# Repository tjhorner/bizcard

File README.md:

# PCBusiness Card

Hiya! Welcome to the documentation for my... business card? Yep, my business card. Which is also a PCB. Chances are you received one from me and are curious enough to scan the QR code on the back.

In these docs, you'll find information on the specs, how to flash it, which peripherals are onboard, how to do cool stuff with it, and (if you received a bare board) where to source the parts you'll need to assemble it. You'll also find the source KiCad project files for the schematic and board, as well as the source for the firmware that is installed by default. These are open source under CC-BY-SA 4.0 and MIT, so feel free to base your own designs on them.

## Directory Structure

- `docs`: Various documents about the project, including hardware info, flashing instructions, etc.
- `firmware`: Default firmware that ships with the board
- `pcb`: KiCad project files for the PCB

## Quick Start

If you want to check out all this board has to offer...

- Look at the docs for the [default firmware](docs/firmware.md). It goes in detail on what it does, and how you can connect to it to your computer via serial to enjoy the whole experience.
- Come back here to dive into the specs, then try your hand at [writing your own firmware](docs/flashing.md) (if you've programmed an Arduino before, it'll be a piece of cake).

After that, it's up to you! You can solder on some GPIO headers and connect whatever the heck you want and make it your own. Blinky Christmas lights? Sure! Doorbell? Why not! Pacemaker? Ok maybe not that. You have the full power of the RP2040 at your disposal, plus a hefty amount of flash you can use to store anything you want.

## Documentation

- [Bill of Materials](docs/bom.md)
- [Flashing Instructions](docs/flashing.md)
- [Schematic](docs/schematic.pdf)
- [FAQ](docs/faq.md)

## Bare Board Assembly

If you received a bare board, you can find the list of parts you will need (and links to where you can buy them) in the [bill of materials](docs/bom.md). At the moment, this assumes you know how to solder really small surface-mount parts (there are a couple of 0402 parts on there)! So this isn't really a beginner project, unfortunately. I might make a through-hole version in the future (or make the SMD pads bigger, I guess), so that it's easier for beginners, but right now you need to be really good at soldering very precisely.

If, for some reason, you really really want an assembled board, there are services out there that will do it for you. Just Google around for "SMT assembly service" and you'll find one. Or you could just ask me. Let me know what you plan to use it for, and if I have any assembled ones lying around I will gladly send one over for you to tinker with! You know how to reach me :)

## Specs

Here is a summary of the things on the board, but you can find more detailed info below:

- **Microcontroller**: [RP2040](https://www.raspberrypi.com/products/rp2040)
- **Flash**: 16MB [W25Q128JVS](http://www.winbond.com/resource-files/w25q128jv_dtr%20revc%2003272018%20plus.pdf)
- **Clock**: 12MHz [X322512MSB4SI](https://lcsc.com/product-detail/SMD-Crystal-Resonators_Yangxing-Tech-X322512MSB4SI_C9002.html) crystal
- **Connectivity**: USB-C 2.0
- **Peripherals**
  - Piezo Buzzer
  - WS2812B (x4)
  - Reset Button
  - USB Boot Button
  - GPIO Headers

### Microcontroller

At the core of the board is an [RP2040](https://www.raspberrypi.com/products/rp2040/), a microcontroller from the same people who make the Raspberry Pi. It was chosen mostly because I heard of it once and decided it would be cool to include in a project, so there it is! It's relatively cheap, but pretty powerful. It is also extremely well-documented and has lots of community support, making it great to write your own firmware for.

- [RP2040 Datasheet](https://datasheets.raspberrypi.com/rp2040/rp2040-datasheet.pdf)
- [RP2040 Documentation](https://www.raspberrypi.com/documentation/microcontrollers/rp2040.html)
- [Official C/C++ SDK](https://www.raspberrypi.com/documentation/microcontrollers/c_sdk.html)
- [Official MicroPython SDK](https://www.raspberrypi.com/documentation/microcontrollers/micropython.html)

### Flash

The prepopulated boards come with a hefty 16MB of onboard QSPI flash provided by the W25Q128JVS chip, which is recommended by the Raspberry Pi Foundation in their hardware design documentation. This means you can include lots of libraries in your code and not have to worry about running out of space. Plus, this is actually the maximum amount of flash storage the RP2040 supports, so you can utilize it to its full potential.

If you have a bare board and don't want to go with the W25Q128JVS, you can use any QSPI flash you want. There are more details in the [RP2040 datasheet](https://datasheets.raspberrypi.com/rp2040/rp2040-datasheet.pdf#section_ssi), under section 4.10.

- [W25Q128JVS Datasheet](http://www.winbond.com/resource-files/w25q128jv_dtr%20revc%2003272018%20plus.pdf)

### Clock

The clock on the prepopulated boards is a 12MHz crystal. There's not much else to say here!

- [X322512MSB4SI Datasheet](https://datasheet.lcsc.com/lcsc/2103291203_Yangxing-Tech-X322512MSB4SI_C9002.pdf)

### Connectivity

In the top-left corner of the board you will find a USB-C receptacle, chosen simply because I really like USB-C, and it's very commonly used in other devices these days, so I'm sure you will have a cable lying around. Conveniently, the RP2040 actually has USB support built-in, so no additional components were required to get it to work.

### Peripherals

I included some peripherals on board so that it's not entirely boring when you plug it in, and if you want to reflash it with your own firmware you already have some stuff to play with!

#### Piezo Buzzer

The buzzer is connected to GPIO3, and is compatible with the Arduino framework's [tone method](https://www.arduino.cc/reference/en/language/functions/advanced-io/tone/), so it's very easy to write code for.

On the prepopulated boards I used [this buzzer](https://lcsc.com/product-detail/Buzzers_CY-Changzhou-Chaoyin-Elec-Cy-SMD-9019-3040_C968734.html) just because it was the first one from JLCPCB that matched the footprint I used. If you have a bare board, you can use any passive 3V 9x9mm SMD buzzer, like [this one](https://www.digikey.com/en/products/detail/cui-devices/CPT-9019S-SMT-TR/6012432) from Digi-Key.

- [Datasheet](https://datasheet.lcsc.com/lcsc/2012111405_CY-Changzhou-Chaoyin-Elec-Cy-SMD-9019-3040_C968734.pdf)

#### WS2812B (aka NeoPixel)

There are four WS2812B RGB LEDs on the top-right of the board connected to GPIO24 that you can do whatever you want with. The cool thing about these LEDs is that they have a built-in driver chip and you can link them together to control as many as you want from just a single data pin. There are a couple of libraries you can use to drive them, but I like Adafruit's [NeoPixel library](https://github.com/adafruit/Adafruit_NeoPixel).

- [WS2812B Datasheet](https://cdn-shop.adafruit.com/datasheets/WS2812B.pdf)

#### Reset & USB Boot Buttons

These aren't peripherals, per se, but I thought I would include them here anyway.

The reset button can be used to restart the RP2040, and the USB boot button can be held during boot to instruct the RP2040 to mount itself as a mass storage device so you can reflash it.

#### GPIO Headers

Also not really a peripheral, but very useful for connecting your own stuff! These are unpopulated by default to keep the profile small, but if you want to turn the card into basically a fully-fledged RP2040 dev board, you can solder some 2.54mm-pitch headers to the unpopulated pads. [Here](https://www.digikey.com/en/products/detail/adam-tech/PH2-12-UA/9830397) is a 2x6 pin header from Digi-Key that should fit nicely. There's also a [socket version](https://www.digikey.com/en/products/detail/sullins-connector-solutions/PPPC062LFBN-RC/810246) similar to what you would find on an Arduino Uno, if you prefer that.

Once you have soldered the headers, you can go ahead and use the labeled GPIO pins to connect whatever other peripherals you want to the board and make it truly your own. Have fun!

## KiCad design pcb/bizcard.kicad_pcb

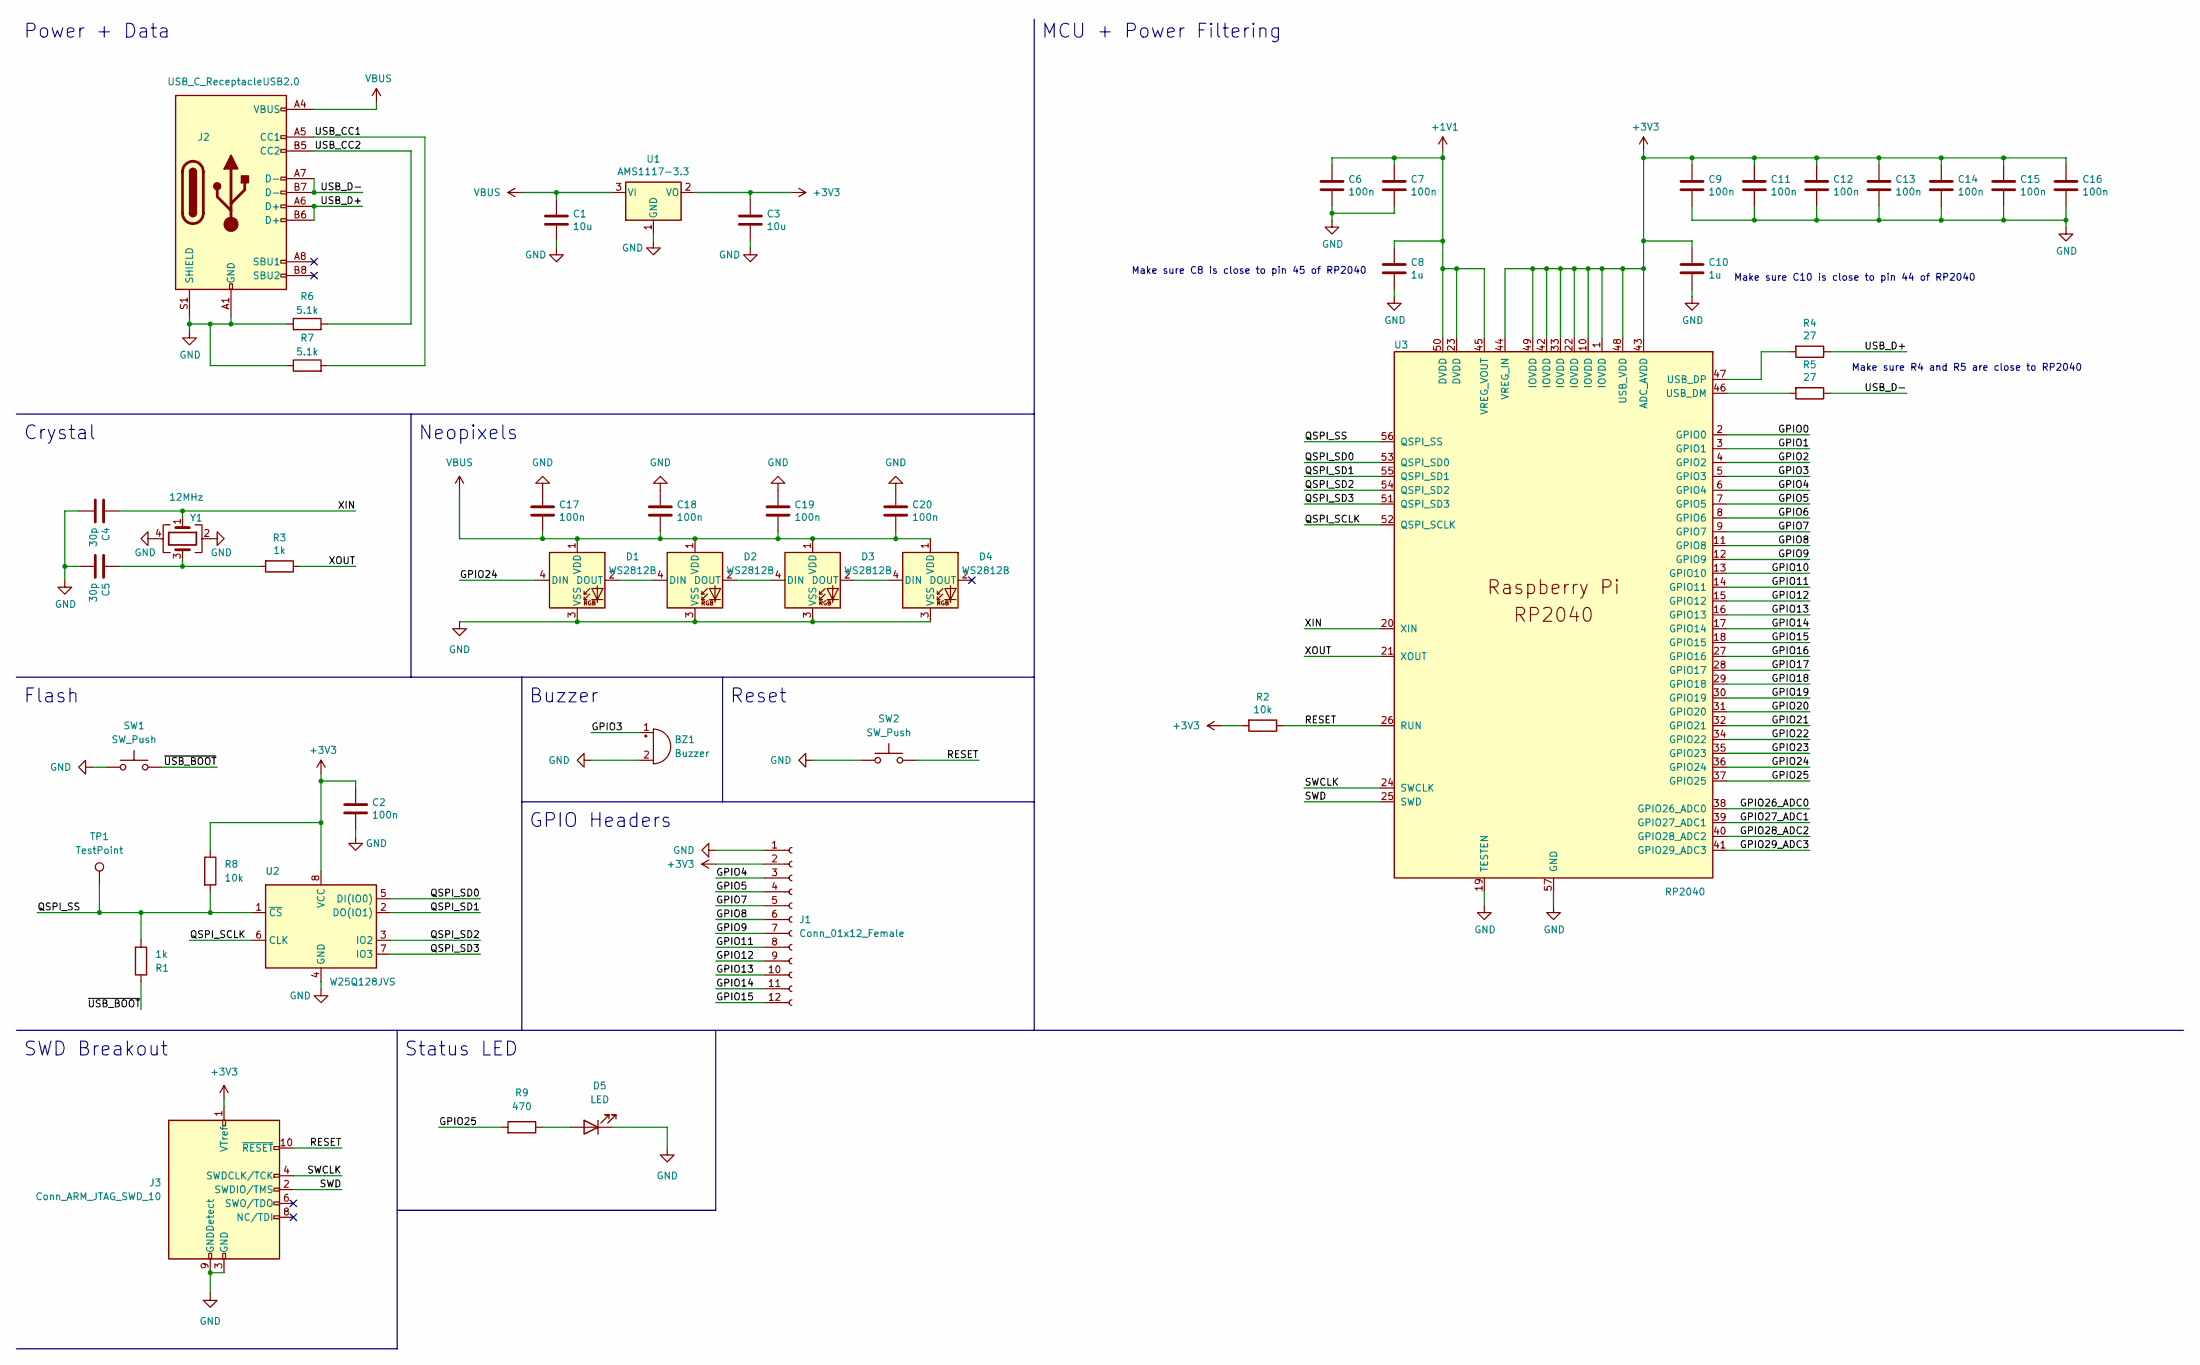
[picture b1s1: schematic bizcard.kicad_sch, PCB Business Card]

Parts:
BZ1: Buzzer; Buzzer_CUI_CPT-9019S-SMT; LCSC C391035
C1, C3: 10u; C_0402_1005Metric; LCSC C15525
C2, C6, C7, C9, C11, C12, C13, C14, C15, C16, C17, C18, C19, C20: 100n; C_0402_1005Metric; LCSC C1525
C4, C5: 30p; C_0402_1005Metric; LCSC C1570
C8, C10: 1u; C_0402_1005Metric; LCSC C52923
D1, D2, D3, D4: WS2812B; LED_WS2812B_PLCC4_5.0x5.0mm_P3.2mm; LCSC C2761795
D5: LED; LED_0603_1608Metric; LCSC C72043
J1: Conn_01x12_Female; PinSocket_2x06_P2.54mm_Vertical
J2: USB_C_ReceptacleUSB2.0; USB_C_Receptacle_Palconn_UTC16-G; LCSC C165948
J3: Conn_ARM_JTAG_SWD_10; PinHeader_2x05_P1.27mm_Vertical_SMD
R1, R3: 1k; R_0402_1005Metric; LCSC C11702
R2, R8: 10k; R_0402_1005Metric; LCSC C25744
R4, R5: 27; R_0603_1608Metric; LCSC C25190
R6, R7: 5.1k; R_0402_1005Metric; LCSC C25905
R9: 470; R_0402_1005Metric; LCSC C25117
SW1, SW2: SW_Push; SW_SPST_TL3342; PARTREV A0; LCSC C318884
TP1: TestPoint; TestPoint_Pad_D2.5mm
U1: AMS1117-3.3; SOT-223-3_TabPin2; LCSC C6186
U2: W25Q128JVS; SOIC-8_5.23x5.23mm_P1.27mm; LCSC C97521
U3: RP2040; RP2040-QFN-56; LCSC C2040
Y1: 12MHz; Crystal_SMD_3225-4Pin_3.2x2.5mm; LCSC C9002

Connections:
+1V1: C6.1, C7.1, C8.1, U3.23 (DVDD), U3.45 (VREG_VOUT), U3.50 (DVDD)
+3V3: C2.1, C3.1, C9.1, C10.1, C11.1, C12.1, C13.1, C14.1, C15.1, C16.1, J1.2, J3.1 (VTref), R2.2, R8.1, U1.2 (VO), U2.8 (VCC), U3.1 (IOVDD), U3.10 (IOVDD), U3.22 (IOVDD), U3.33 (IOVDD), U3.42 (IOVDD), U3.43 (ADC_AVDD), U3.44 (VREG_IN), U3.48 (USB_VDD), U3.49 (IOVDD)
/GPIO0: U3.2 (GPIO0)
/GPIO1: U3.3 (GPIO1)
/GPIO2: U3.4 (GPIO2)
/GPIO3: BZ1.1 (-), U3.5 (GPIO3)
/GPIO4: J1.3, U3.6 (GPIO4)
/GPIO5: J1.4, U3.7 (GPIO5)
/GPIO6: U3.8 (GPIO6)
/GPIO7: J1.5, U3.9 (GPIO7)
/GPIO8: J1.6, U3.11 (GPIO8)
/GPIO9: J1.7, U3.12 (GPIO9)
/GPIO10: U3.13 (GPIO10)
/GPIO11: J1.8, U3.14 (GPIO11)
/GPIO12: J1.9, U3.15 (GPIO12)
/GPIO13: J1.10, U3.16 (GPIO13)
/GPIO14: J1.11, U3.17 (GPIO14)
/GPIO15: J1.12, U3.18 (GPIO15)
/GPIO16: U3.27 (GPIO16)
/GPIO17: U3.28 (GPIO17)
/GPIO18: U3.29 (GPIO18)
/GPIO19: U3.30 (GPIO19)
/GPIO20: U3.31 (GPIO20)
/GPIO21: U3.32 (GPIO21)
/GPIO22: U3.34 (GPIO22)
/GPIO23: U3.35 (GPIO23)
/GPIO24: D1.4 (DIN), U3.36 (GPIO24)
/GPIO25: R9.2, U3.37 (GPIO25)
/GPIO26_ADC0: U3.38 (GPIO26_ADC0)
/GPIO27_ADC1: U3.39 (GPIO27_ADC1)
/GPIO28_ADC2: U3.40 (GPIO28_ADC2)
/GPIO29_ADC3: U3.41 (GPIO29_ADC3)
/QSPI_SCLK: U2.6 (CLK), U3.52 (QSPI_SCLK)
/QSPI_SD0: U2.5 (DI(IO0)), U3.53 (QSPI_SD0)
/QSPI_SD1: U2.2 (DO(IO1)), U3.55 (QSPI_SD1)
/QSPI_SD2: U2.3 (IO2), U3.54 (QSPI_SD2)
/QSPI_SD3: U2.7 (IO3), U3.51 (QSPI_SD3)
/QSPI_SS: R1.2, R8.2, TP1.1, U2.1 (~CS), U3.56 (QSPI_SS)
/RESET: J3.10 (~RESET), R2.1, SW2.2, U3.26 (RUN)
/SWCLK: J3.4 (SWDCLK/TCK), U3.24 (SWCLK)
/SWD: J3.2 (SWDIO/TMS), U3.25 (SWD)
/USB_CC1: J2.A5 (CC1), R7.2
/USB_CC2: J2.B5 (CC2), R6.2
/USB_D+: J2.A6 (D+), J2.B6 (D+), R4.1
/USB_D-: J2.A7 (D-), J2.B7 (D-), R5.1
/XIN: C4.1, U3.20 (XIN), Y1.1
/XOUT: R3.1, U3.21 (XOUT)
/~USB_BOOT: R1.1, SW1.2
GND: BZ1.2 (+), C1.2, C2.2, C3.2, C4.2, C5.2, C6.2, C7.2, C8.2, C9.2, C10.2, C11.2, C12.2, C13.2, C14.2, C15.2, C16.2, C17.1, C18.1, C19.1, C20.1, D1.3 (VSS), D2.3 (VSS), D3.3 (VSS), D4.3 (VSS), D5.1 (K), J1.1, J2.A1 (GND), J2.A12 (GND), J2.B1 (GND), J2.B12 (GND), J2.S1 (SHIELD), J3.3 (GND), J3.5 (GND), J3.9 (GNDDetect), R6.1, R7.1, SW1.1, SW2.1, U1.1 (GND), U2.4 (GND), U3.19 (TESTEN), U3.57 (GND), Y1.2, Y1.4
unnamed: C5.1, R3.2, Y1.3
unnamed: D1.2 (DOUT), D2.4 (DIN)
unnamed: D2.2 (DOUT), D3.4 (DIN)
unnamed: D3.2 (DOUT), D4.4 (DIN)
unnamed: D5.2 (A), R9.1
unnamed: R4.2, U3.47 (USB_DP)
unnamed: R5.2, U3.46 (USB_DM)
VBUS: C1.1, C17.2, C18.2, C19.2, C20.2, D1.1 (VDD), D2.1 (VDD), D3.1 (VDD), D4.1 (VDD), J2.A4 (VBUS), J2.A9 (VBUS), J2.B4 (VBUS), J2.B9 (VBUS), U1.3 (VI)

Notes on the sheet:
Status LED
Make sure C8 is close to pin 45 of RP2040
Neopixels
MCU + Power Filtering
Power + Data
Reset
SWD Breakout
Buzzer
Make sure C10 is close to pin 44 of RP2040
GPIO Headers
Crystal
Make sure R4 and R5 are close to RP2040
Flash

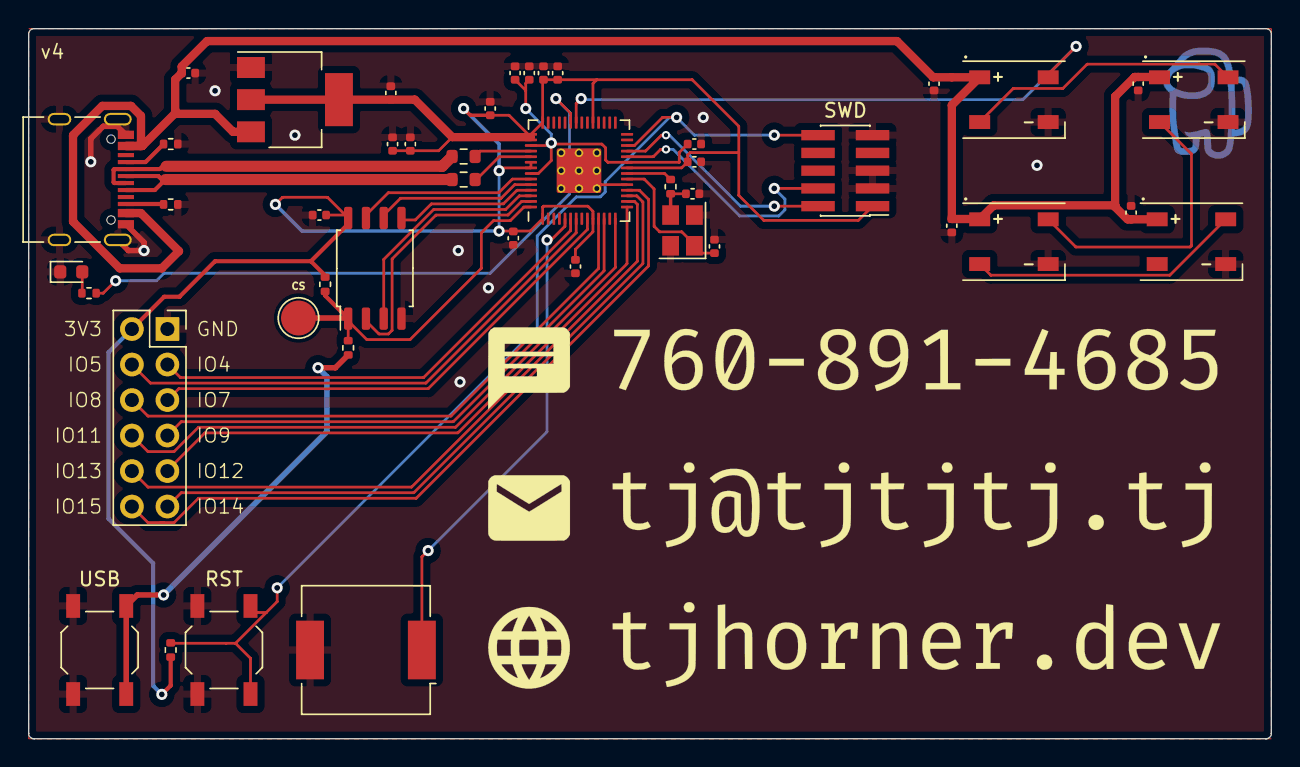
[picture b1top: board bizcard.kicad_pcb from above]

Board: 2 copper layers, 88.9 x 50.8 mm, 49 parts (0 on the bottom side), 40 nets.

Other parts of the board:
Ref**: Val**; info
Ref**#2: Val**; amongy
Ref**#3: Val**; qrcode_smaller
Ref**#4: Val**; name_smaller

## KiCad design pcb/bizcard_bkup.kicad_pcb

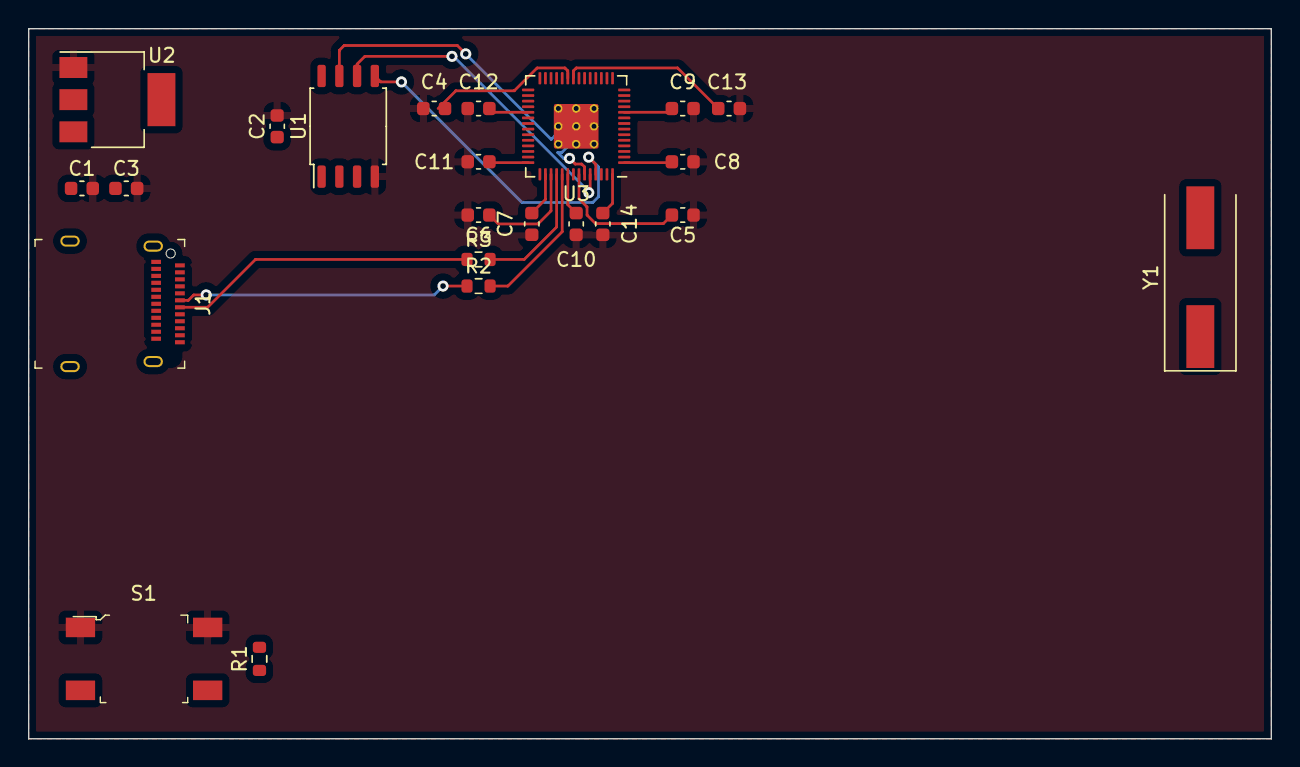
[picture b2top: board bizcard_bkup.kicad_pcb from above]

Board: 2 copper layers, 88.9 x 50.8 mm, 25 parts (0 on the bottom side), 16 nets.

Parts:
C1, C3: 10uF; C_0603_1608Metric
C2, C4, C5, C8, C9, C10, C11, C12, C13, C14: 100nF; C_0603_1608Metric
C6, C7: 1uF; C_0603_1608Metric
J1: USB_C_Receptacle; USB-C_Female_12401X
R1: 1k; R_0603_1608Metric
R2, R3: 27.4; R_0603_1608Metric
Ref**: Val**; name
Ref**#2: Val**; info
S1: FSM4JSMATR; Switch_Tactile_SMD_6x6mm
U1: W25Q128JVS; SOIC-8_5.23x5.23mm_P1.27mm
U2: NCP1117-3.3_SOT223; SOT-223-3_TabPin2
U3: RP2040; RP2040-QFN-56
Y1: ABLS-12.000MHZ-B4-T; Crystal_SMD_HC49-SD

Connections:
+1V1: C4.2, C5.2, C6.1, U3.23 (DVDD), U3.45 (VREG_VOUT), U3.50 (DVDD)
+3V3: C2.1, C3.1, C7.1, C8.1, C9.1, C10.1, C11.1, C12.1, C13.1, C14.1, R1.2, U1.1 (~CS), U1.8 (VCC), U2.2 (VO), U3.1 (IOVDD), U3.10 (IOVDD), U3.22 (IOVDD), U3.33 (IOVDD), U3.42 (IOVDD), U3.43 (ADC_AVDD), U3.44 (VREG_IN), U3.48 (USB_VDD), U3.49 (IOVDD), U3.56 (QSPI_SS)
/QSPI_CLK: U1.6 (CLK), U3.52 (QSPI_SCLK)
/USB_D+: J1.A6 (D+), J1.B6 (D+), R2.1
/USB_D-: J1.A7 (D-), J1.B7 (D-), R3.1
/XIN: U3.20 (XIN), Y1.1
/XOUT: U3.21 (XOUT), Y1.2
GND: C1.2, C2.2, C3.2, C4.1, C5.1, C6.2, C7.2, C8.2, C9.2, C10.2, C11.2, C12.2, C13.2, C14.2, J1.A1 (GND), J1.A12 (GND), J1.B1 (GND), J1.B12 (GND), S1.1, S1.2, U1.4 (GND), U2.1 (GND)
unnamed: R1.1, S1.3, S1.4
unnamed: R2.2, U3.47 (USB_DP)
unnamed: R3.2, U3.46 (USB_DM)
unnamed: U1.2 (DO(IO1)), U3.55 (QSPI_SD1)
unnamed: U1.3 (IO2), U3.54 (QSPI_SD2)
unnamed: U1.5 (DI(IO0)), U3.53 (QSPI_SD0)
unnamed: U1.7 (IO3), U3.51 (QSPI_SD3)
VBUS: C1.1, J1.A4 (VBUS), J1.A9 (VBUS), J1.B4 (VBUS), J1.B9 (VBUS), U2.3 (VI)

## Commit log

2022-04-12 and there we go
2022-04-12 sigh
2022-04-12 barebones template for firmware
2022-04-12 fix schematic
2022-04-12 add licenses
2022-04-12 update main license
2022-04-23 slight updates

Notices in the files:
pcb/bizcard.kicad_sch:
License: CC-BY-SA 4.0
